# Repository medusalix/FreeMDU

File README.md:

# FreeMDU 

The FreeMDU project provides open hardware and software tools for communicating with Miele appliances via their optical diagnostic interface. It serves as a free and open alternative to the proprietary **Miele Diagnostic Utility (MDU)** software, which is only available to registered service technicians.

Most Miele devices manufactured after 1996 include an optical infrared-based diagnostic interface, hidden behind one of the indicator lights on the front panel. On older appliances, this interface is marked by a **Program Correction (PC)** label.

Until now, communication with this interface required an expensive infrared adapter sold exclusively by Miele, along with their closed-source software. The goal of FreeMDU is to make this interface accessible to everyone for diagnostic and home automation purposes.

The project is split into three main components:

- [**Protocol**](protocol): core protocol library and device implementations
- [**TUI**](tui): terminal-based device diagnostic and testing tool
- [**Home**](home): communication adapter firmware with MQTT integration for Home Assistant
- [**ESPHome**](esphome): ESPHome component built on the protocol library, an alternative to the home firmware's standalone mode

More details about the proprietary diagnostic interface and the reverse-engineering process behind this project can be found in this [**blog post**](https://medusalix.github.io/posts/miele-interface).

> [!CAUTION]
> This project is highly experimental and can cause permanent damage to your Miele devices if not used responsibly. Proceed at your own risk.

## Supported devices

When a connection is established via the diagnostic interface, the appliance responds with its **software ID**, a 16-bit number that uniquely identifies the firmware version running on the device's microcontroller. However, this ID does not directly correspond to a specific model or board type, so it's impossible to provide a comprehensive list of supported models.

The following table lists the software IDs and device/board combinations that have been confirmed to work with FreeMDU:

| Software ID | Device         | Board      | Microcontroller           | Optical interface location   | Status             |
|-------------|----------------|------------|---------------------------|------------------------------|--------------------|
| 218         | W 985          | EDPW 213   | Mitsubishi M37451MC       | *Check inlet (PC)* indicator | 🟢 Fully supported |
| 324         | W 980          | EDPW 213   | Mitsubishi M37451MC       | *Check inlet (PC)* indicator | 🟢 Fully supported |
| 360         | Bare board     | EDPW 223-A | Mitsubishi M38078MC-065FP | *Check inlet (PC)* indicator | 🟢 Fully supported |
| 419         | Bare board     | EDPW 206   | Mitsubishi M37451MC-804FP | *Check inlet (PC)* indicator | 🟢 Fully supported |
| 457         | W 471          | Unknown    | Unknown                   | *Check inlet (PC)* indicator | 🟡 Read-only       |
| 469         | W 487 S        | EDPW 228-A | Mitsubishi M38078MF       | *Check inlet (PC)* indicator | 🟢 Fully supported |
| 517         | G 7804         | EGPL 061   | Mitsubishi M38079EFFP     | *(PC) DOS* indicator         | 🟢 Fully supported |
| 605         | G 651 I PLUS-3 | EGPL 542-C | Mitsubishi M38027M8       | *Salt (PC)* indicator        | 🟢 Fully supported |
| 629         | W 2446         | EDPL 126-B | Mitsubishi M38079MF-308FP | *Check inlet (PC)* indicator | 🟢 Fully supported |
| 2088        | W 3241         | EDPL 162-B | Mitsubishi M38079EFFP     | *Check inlet (PC)* indicator | 🟢 Fully supported |
| 2895        | W 3164         | EDPL 151-B | Mitsubishi M38079MF-322FP | *Check inlet (PC)* indicator | 🟢 Fully supported |

If your appliance is not listed here but has a model number similar to one of the above, it might already be compatible. In all other cases, determining the **software ID** is the first step toward adding support for new devices.

Details for adding support for new devices will be provided soon.

## Getting started

Before using any FreeMDU components, make sure you have the [Rust toolchain](https://rust-lang.org/tools/install) installed on your system.

Next, you'll need to build a [communication adapter](home/README.md#getting-started) to interface with your Miele device. Once the adapter is ready, choose the appropriate use case from the options below:

### Device diagnostics and testing

If you want to repair or test your appliance:

1. Flash the [home](home) firmware in **bridge mode** onto your communication adapter and attach it to your device.

2. Run the [TUI](tui) application on your desktop computer.

### Integration into home automation systems

If you want to integrate your appliance into **Home Assistant** or another home automation system:

1. Flash the [home](home) firmware in **standalone mode** onto your communication adapter and attach it to your device.

   If you already use **ESPHome**, the [ESPHome component](esphome) is an alternative with over-the-air updates and the native Home Assistant API.

### Building custom tools

If you want to develop your own software to communicate with Miele devices:

1. Flash the [home](home) firmware in **bridge mode** onto your communication adapter and attach it to your device.

2. Use the [protocol](protocol) crate to implement your custom software.

## Disclaimer

This is an independent, open-source project and is **not affiliated with, endorsed by, or sponsored by Miele & Cie. KG** or its affiliates. All product names and trademarks are the property of their respective owners. References to Miele appliances are for descriptive purposes only and do not imply any association with Miele.

## License

Licensed under either of

- Apache License, Version 2.0 ([LICENSE-APACHE](LICENSE-APACHE) or <http://www.apache.org/licenses/LICENSE-2.0>)
- MIT license ([LICENSE-MIT](LICENSE-MIT) or <http://opensource.org/licenses/MIT>)

at your option.

## Contribution

Unless you explicitly state otherwise, any contribution intentionally submitted for inclusion in the work by you, as defined in the Apache-2.0 license, shall be dual licensed as above, without any additional terms or conditions.

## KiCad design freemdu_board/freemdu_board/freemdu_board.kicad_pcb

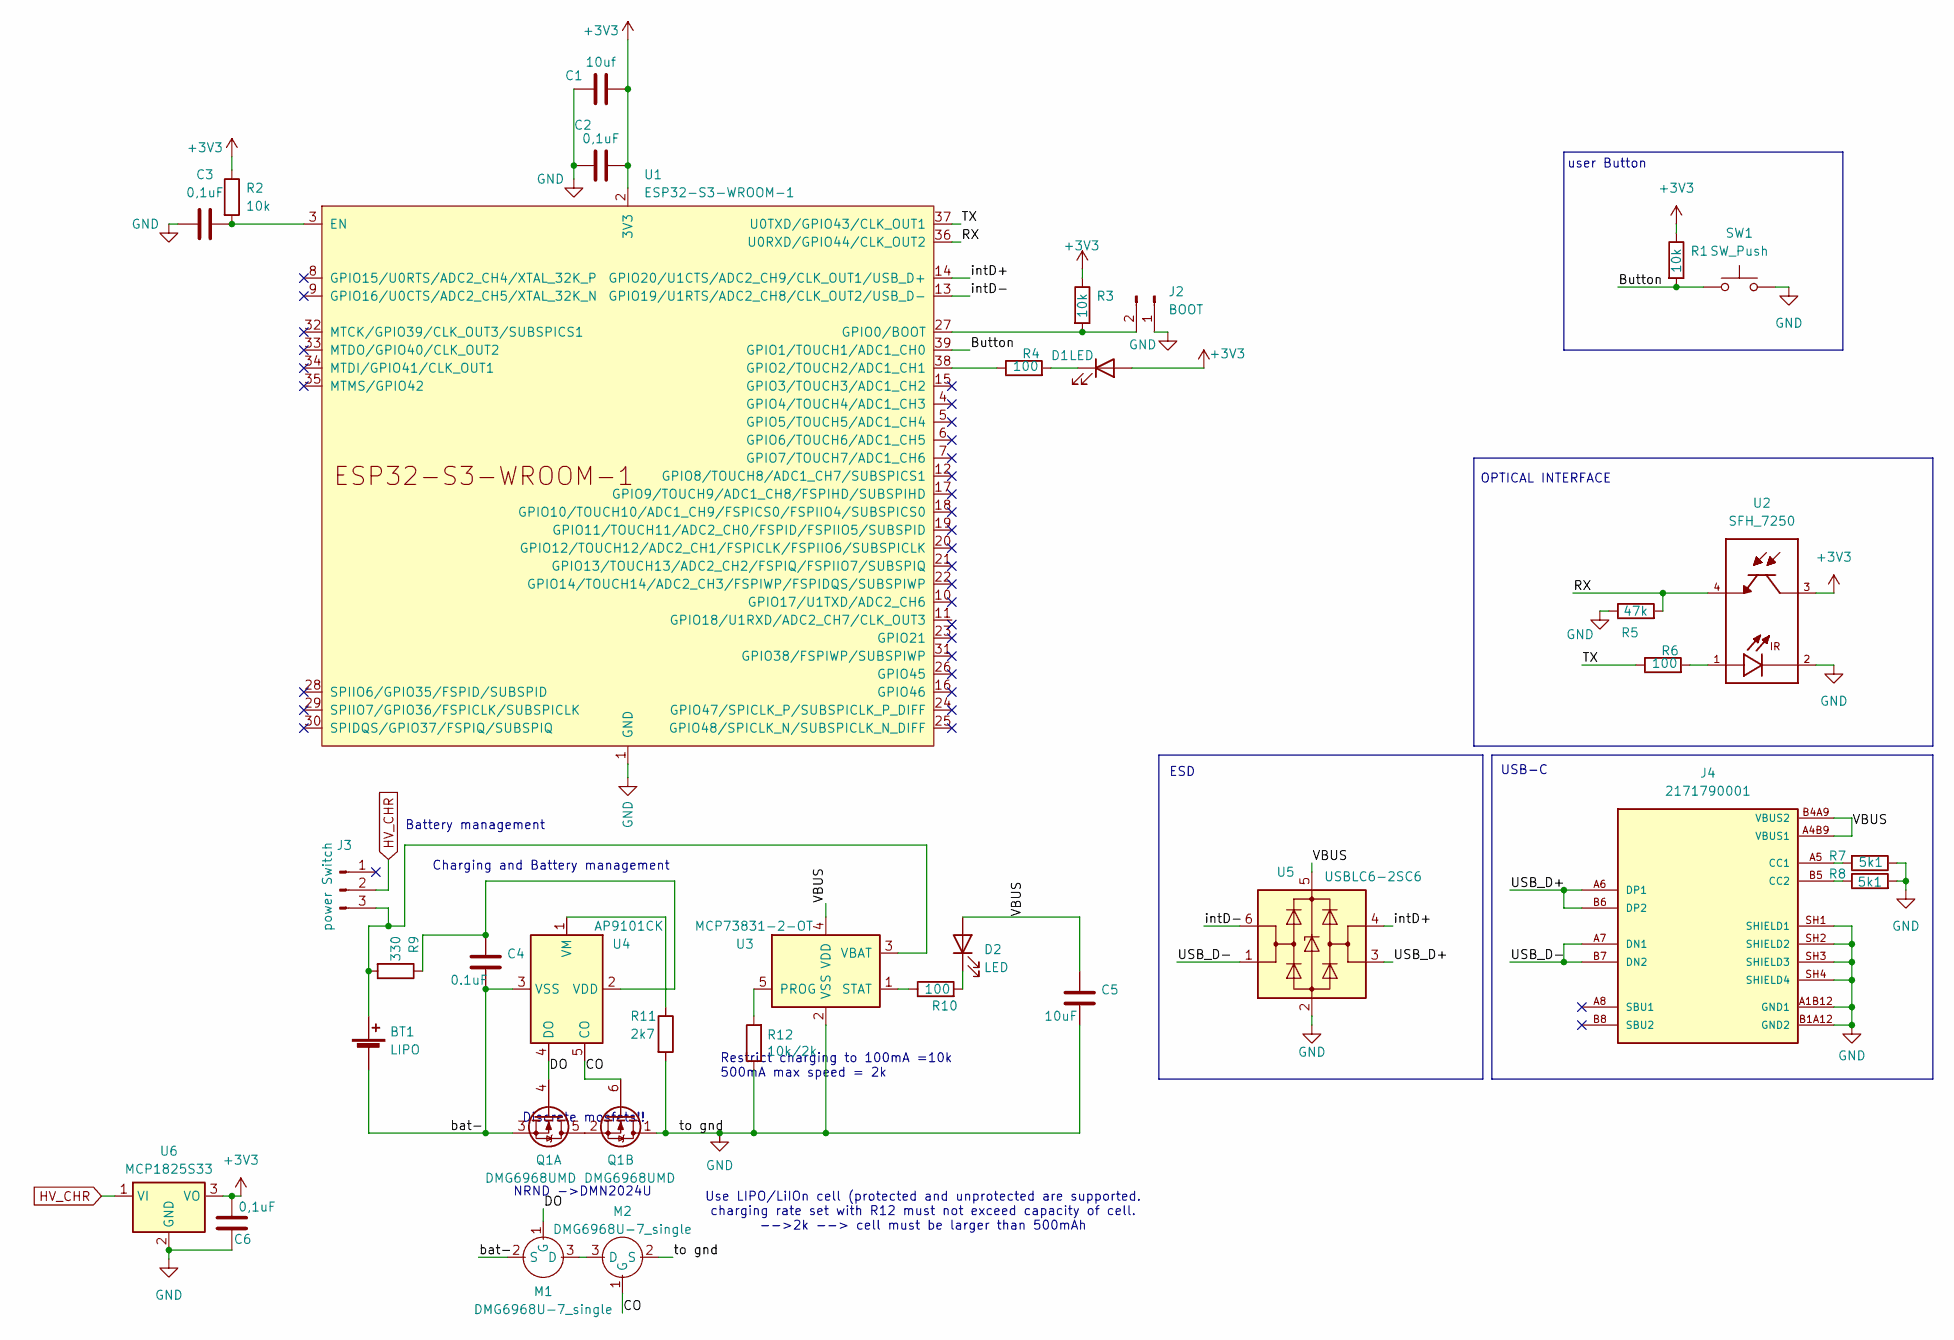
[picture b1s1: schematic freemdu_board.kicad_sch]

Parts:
BT1: LIPO; PinHeader_1x02_P2.54mm_Vertical
C1: 10uf; C_0603_1608Metric
C2, C3, C6: 0,1uF; C_0603_1608Metric
C4: 0.1uF; C_0603_1608Metric
C5: 10uF; C_0603_1608Metric
D1, D2: LED; LED_0603_1608Metric
J2: BOOT; PinHeader_1x02_P2.54mm_Horizontal
J3: power Switch; PinHeader_1x03_P2.54mm_Vertical
J4: 2171790001; MOLEX_2171790001; PARTREV A1
M1, M2: DMG6968U-7_single; TSOT-23
Q1: DMG6968UMD; SOT-23-6_Handsoldering
R1, R2, R3: 10k; R_0603_1608Metric
R4, R6, R10: 100; R_0603_1608Metric
R5: 47k; R_0603_1608Metric
R7, R8: 5k1; R_0603_1608Metric
R9: 330; R_0603_1608Metric
R11: 2k7; R_0603_1608Metric
R12: 10k/2k; R_0603_1608Metric
SW1: SW_Push; SW_SPST_EVQP0
U1: ESP32-S3-WROOM-1
U2: SFH_7250; OSRAM_SFH_7250; PARTREV 1.3
U3: MCP73831-2-OT; SOT-23-5
U4: AP9101CK; SOT-23-5
U5: USBLC6-2SC6; SOT-23-6
U6: MCP1825S33; SOT-223-3_TabPin2

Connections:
+3V3: C1.2, C2.2, C6.1, D1.2 (A), R1.1, R2.1, R3.1, U1.2 (3V3), U2.3, U6.3 (VO)
/Button: R1.2, SW1.1, U1.39 (GPIO1/TOUCH1/ADC1_CH0)
/CO: M2.1 (G), Q1.6 (G), U4.5 (CO)
/DO: M1.1 (G), Q1.4 (G), U4.4 (DO)
/RX: R5.2, U1.36 (U0RXD/GPIO44/CLK_OUT2), U2.4
/TX: R6.1, U1.37 (U0TXD/GPIO43/CLK_OUT1)
/USB_D+: J4.A6 (DP1), J4.B6 (DP2), U5.3 (I/O2)
/USB_D-: J4.A7 (DN1), J4.B7 (DN2), U5.1 (I/O1)
/VBUS: C5.1, D2.2 (A), J4.A4B9 (VBUS1), J4.B4A9 (VBUS2), U3.4 (VDD), U5.5 (VBUS)
/bat-: BT1.2 (-), C4.2, M1.2 (S), Q1.3 (S), U4.3 (VSS)
/intD+: U1.14 (GPIO20/U1CTS/ADC2_CH9/CLK_OUT1/USB_D+), U5.4 (I/O2)
/intD-: U1.13 (GPIO19/U1RTS/ADC2_CH8/CLK_OUT2/USB_D-), U5.6 (I/O1)
GND: C1.1, C2.1, C3.1, C5.2, C6.2, J2.1, J4.A1B12 (GND1), J4.B1A12 (GND2), J4.SH1 (SHIELD1), J4.SH2 (SHIELD2), J4.SH3 (SHIELD3), J4.SH4 (SHIELD4), M2.2 (S), Q1.1 (D), R5.1, R7.1, R8.2, R11.2, R12.1, SW1.2, U1.1 (GND), U1.40 (GND), U1.41 (GND), U2.2, U3.2 (VSS), U5.2 (GND), U6.2 (GND)
HV_CHR: J3.2, U6.1 (VI)
unnamed: BT1.1 (+), J3.3, R9.2, U3.3 (VBAT)
unnamed: D1.1 (K), R4.2
unnamed: D2.1 (K), R10.2
unnamed: J2.2, R3.2, U1.27 (GPIO0/BOOT)
unnamed: J4.A5 (CC1), R7.2
unnamed: J4.B5 (CC2), R8.1
unnamed: M1.3 (D), M2.3 (D)
unnamed: Q1.2 (S), Q1.5 (D)
unnamed: R6.2, U2.1
unnamed: C3.2, R2.2, U1.3 (EN)
unnamed: R4.1, U1.38 (GPIO2/TOUCH2/ADC1_CH1)
unnamed: R12.2, U3.5 (PROG)
unnamed: R10.1, U3.1 (STAT)
unnamed: C4.1, R9.1, U4.2 (VDD)
unnamed: R11.1, U4.1 (VM)

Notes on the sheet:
Charging and Battery management
ESD
OPTICAL INTERFACE
USB-C
Discrete mosfets!!
NRND ->DMN2024U
Battery management
Restrict charging to 100mA =10k 500mA max speed = 2k
Use LIPO/LiIOn cell (protected and unprotected are supported. charging rate set with R12 must not exceed capacity of cell. -->2k --> cell must be larger than 500mAh
user Button

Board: 2 copper layers, 33 parts (0 on the bottom side), 28 nets, no tracks yet.

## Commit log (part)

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2025-11-20 Add links to README badges
2025-12-30 Add support for W627F washing machine
    This commit introduces support for the W627F series washing machines with software ID 1998. A new module, `id1998.rs`, has been added, containing the implementation for device interaction, including 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
    Next Steps for @Martinius
    After building with cargo build, the dump programs should now work:
    cargo run --example dump_memory -- /dev/ttyACM0 memory.bin
    cargo run --example dump_eeprom -- /dev/ttyA
2026-01-16 Add support for ID 324
2026-01-17 Add program spin speed property
2026-01-17 Add motor PWM duty cycle property
2026-01-17 Fix load level comment
2026-01-17 Add motor protection relay actuator
2026-01-17 Fix operating mode comments
2026-01-17 Fix faults
2026-01-17 Fix lints
2026-01-17 Add door open operating mode
2026-01-17 Add ring illumination actuator
2026-01-19 Fix README typo
2026-01-19 Update Ratatui version
2026-01-19 Apply small corrections
2026-01-19 Simplify binary value parsing
2026-01-19 Add support for WS2812 RGB led
2026-01-20 Fix fault handling
2026-01-20 id605, id629: Remove board number property
    This property is not really helpful for diagnostics.
2026-01-20 Add date property value
2026-01-20 id360, id419, id629: Add spin speed property
2026-01-20 id360, id605, id629: Add manufacturing date prop
2026-01-20 id360, id629: Fix tachometer speed
2026-01-20 id360, id629: Add motor target speed property
2026-01-20 id629: Add water diverter position property
2026-01-20 id360, id629: Fix actuator flags
2026-01-20 id360, id629: Add imbalance speed limit property
2026-01-20 id360: Add serial & model number properties
2026-01-20 Handle dates when publishing MQTT values
2026-01-20 id324: Add initial support
2026-01-21 Remove EEPROM read/write restrictions
    Newer devices don't have these restrictions anymore.
2026-01-21 id1998: Add initial support
2026-01-22 match old code for non-smart case
2026-01-23 Add support for ID 132
2026-01-25 id629: Clarify how actuators work
2026-01-25 Change protocol log level to trace
2026-01-27 Implement extended protocol command set
2026-01-27 Update dump examples for 32-bit reads
2026-01-27 Set min stack size for tests
2026-01-28 Add support for ID 469
2026-01-28 Fix actuators
2026-01-30 id360: Remove serial & model number properties
    It turns out these properties are not available on
    this device, even though the EEPROM is large enough.
2026-01-30 id360: Fix inconsistent literal size
2026-01-30 id360: Add `DoorOpen` operating mode
    The microcontroller resets if the mains frequency is absent
    and enters the `DoorOpen` mode.
2026-01-30 Remove dummy bytes quirk
    This was apparently only required for ID 419 when connected via UART,
    not when using the optical interface.
2026-01-30 TODO: comments
2026-02-02 Add RPM conversion function for VFD motors
2026-02-02 id469: Add initial support
2026-02-04 protocol: try known keys first
2026-02-05 reformatted find_keys
2026-02-05 add arguments for start/end address, tty port, output file and byte address
2026-02-05 add clap only as dev-dependency
2026-02-06 Increase stack size for CI tests
2026-02-06 Implement 32-bit memory access
2026-02-07 Add operating time property
2026-02-08 id419: Add tachometer speed property
2026-02-09 move examples to src/bin, add command line arguments, and add clap as optional dependency
2026-02-12 Change border type for table and popup
2026-02-12 tui: Use paragraph widget for action prompts
    Split message into multiple lines if too long.
2026-02-12 Remove `PROP_STORED_FAULTS`
2026-02-12 Add cell type for property table
2026-02-12 Add device fault type
2026-02-12 id469: Add fault properties
2026-02-12 id629: Add fault properties
2026-02-12 Rename `PropertyKind::Failure` to `Fault`
2026-02-12 id419: Add fault properties
2026-02-12 id605: Add fault properties
2026-02-12 id360: Add fault properties
2026-02-12 Fix property match statement
2026-02-13 Rename `PROP_PROGRAM_SELECTOR`
2026-02-13 id605: Add `Program` enum
2026-02-13 Implement auto-reconnect for TUI
2026-02-14 print ID in decimal, not hex
2026-02-14 Rename `UnknownResponseCode` error
2026-02-14 Add support for configurable baud rates
2026-02-15 id2088: Add initial support
2026-02-18 Implement adjustable chunk sizes
2026-02-18 Implement device reset
2026-02-18 Fix test lints
2026-02-18 Add new functions to `unlock_full_access` docs
2026-02-18 Correct payload length limitation docs
2026-02-18 Implement smart home commands
2026-02-20 Add payload conversions for i8, i16, i32
2026-02-20 Add more properties
2026-02-20 Ignore missing docs for now
2026-02-20 id132: Add initial support
2026-03-06 Add `ACTION_SELECT_PROGRAM`
2026-03-06 Parse operating state
2026-03-20 Implement TUI auto-reconnect
2026-03-22 Support for washing machine W3164, ID 2895. Derived from ID 2088.
2026-03-28 Build fix
2026-03-29 id517: Add initial support
2026-03-30 Add keys for ID 517 to find_keys.rs
2026-03-30 Add machine number property
2026-03-31 Add keys for ID 266
2026-04-03 Extract device utilities module into file
2026-04-04 Add door open operating mode for all devices
2026-04-04 Remove redundant enum discriminants
2026-04-04 Add fault code discriminants
2026-04-04 Simplify fault querying logic
2026-04-04 id324: Add fault properties
2026-04-06 Move `compute_checksum` function into `Interface`
2026-04-06 Clean up interface tests
2026-04-06 Fix `rpm_from_motor_speed_vfd` integer overflow
2026-04-06 Rename operating mode to state
2026-04-06 Change `rpm_from_motor_speed` return type to u16
2026-04-06 Add display decoding helper
2026-04-06 Make `trigger_action` accept a string parameter
2026-04-06 Add tests for utility functions
2026-04-07 Add common definitions for newer devices
2026-04-07 Add range parameters for actions
2026-04-11 Add missing newline
2026-04-14 Update dependencies
2026-04-14 tui: Use Tokio's local runtime
2026-04-15 id2895: Add initial support
2026-04-15 id218: Add initial support
2026-04-25 id517: Add operating time property
2026-04-25 Remove device-specific examples
    A single example in `lib.rs` is sufficient.
2026-04-30 home: Update dependencies
2026-05-03 id360, id469: Fix actuators and add water diverter
    These machines use a water diverter by default.
